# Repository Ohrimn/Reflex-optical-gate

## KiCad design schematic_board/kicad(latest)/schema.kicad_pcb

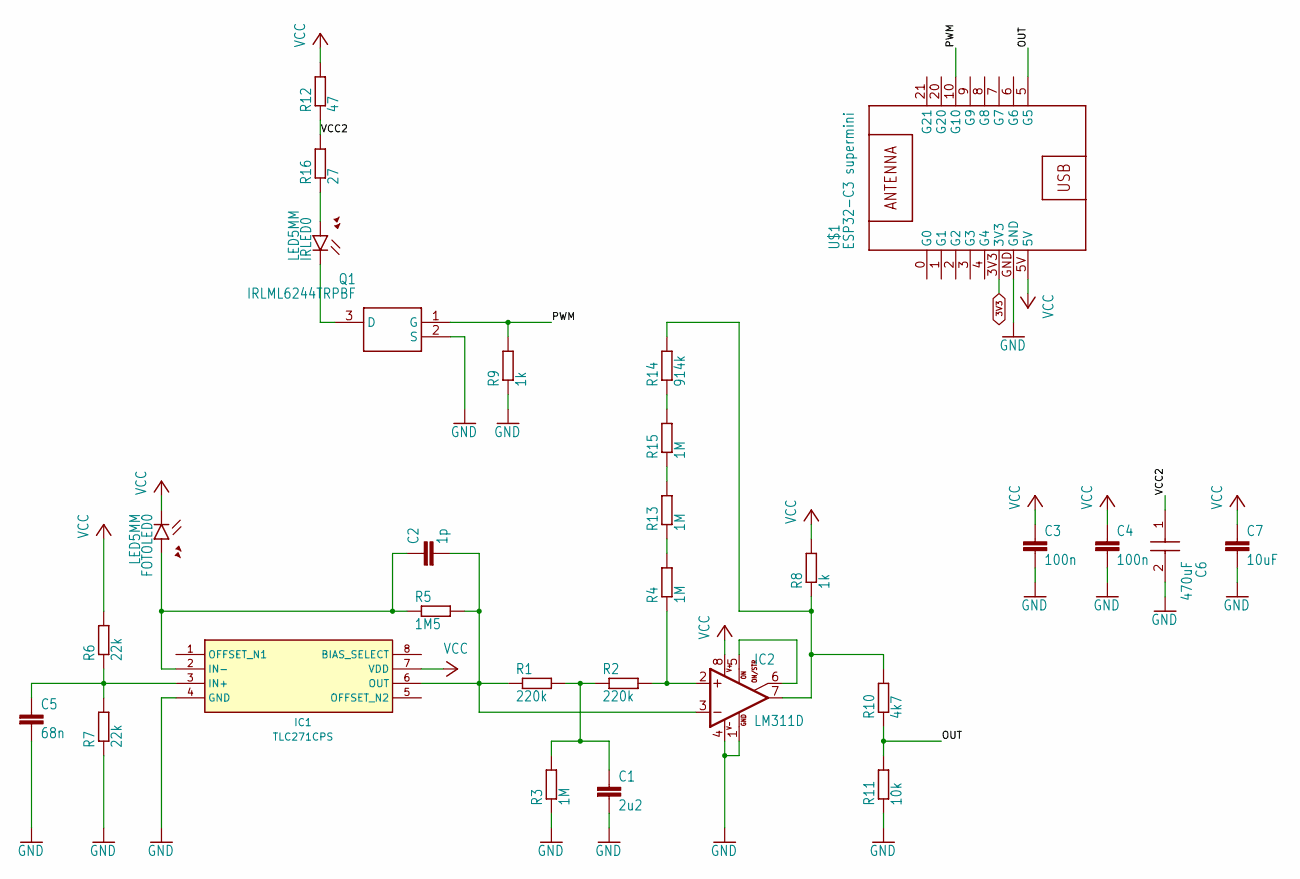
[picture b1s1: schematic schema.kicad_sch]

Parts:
C1: 2u2; C0603
C2: 1p; C0603K
C3, C4: 100n; C0603
C5: 68n; C0603
C6: 470uF; CAPAE830X1100N
C7: 10uF; C0603
FOTOLED0: LED5MM
IC1: TLC271CPS; SOIC-8_3.9x4.9mm_P1.27mm; Mouser Part Number 595-TLC271CPS
IC2: LM311D; SO08
IRLED0: LED5MM
Q1: IRLML6244TRPBF; SOT95P237X112-3N
R1, R2: 220k; R0603
R3, R4, R13, R15: 1M; R0603
R5: 1M5; R0603
R6, R7: 22k; R0603
R8, R9: 1k; R0603
R10: 4k7; R0603
R11: 10k; R0603
R12: 47; R0805
R14: 914k; R0603
R16: 27; R0805
U$1: ESP32-C3 supermini; ESP32-C3_SUPERMINI

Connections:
3V3: U$1.3V3
/OUT: R10.1, R11.2, U$1.5 (G5)
/PWM: Q1.1 (G), R9.2, U$1.10 (G10)
/VCC2: C6.1 (+), R12.1, R16.2
GND: C1.2, C3.2, C4.2, C5.2, C6.2 (-), C7.2, IC1.4 (GND), IC2.1 (GND), IC2.4 (V-), Q1.2 (S), R3.1, R7.1, R9.1, R11.1, U$1.GND
unnamed: C1.1, R1.2, R2.1, R3.2
unnamed: C5.1, IC1.3 (IN+), R6.1, R7.2
unnamed: C2.1, FOTOLED0.A, IC1.2 (IN-), R5.1
unnamed: C2.2, IC1.6 (OUT), IC2.3 (-IN), R1.1, R5.2
unnamed: IC2.2 (+IN), R2.2, R4.1
unnamed: IC2.5 (ON), IC2.6 (ON/STR)
unnamed: IC2.7 (OUT), R8.1, R10.2, R14.2
unnamed: IRLED0.K (C), Q1.3 (D)
unnamed: IRLED0.A, R16.1
unnamed: R4.2, R13.1
unnamed: R13.2, R15.1
unnamed: R14.1, R15.2
VCC: C3.1, C4.1, C7.1, FOTOLED0.K (C), IC1.7 (VDD), IC2.8 (V+), R6.2, R8.2, R12.2, U$1.5V

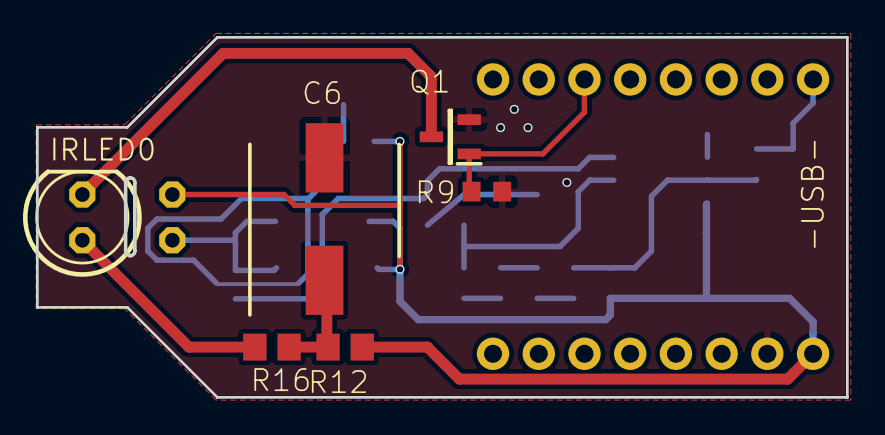
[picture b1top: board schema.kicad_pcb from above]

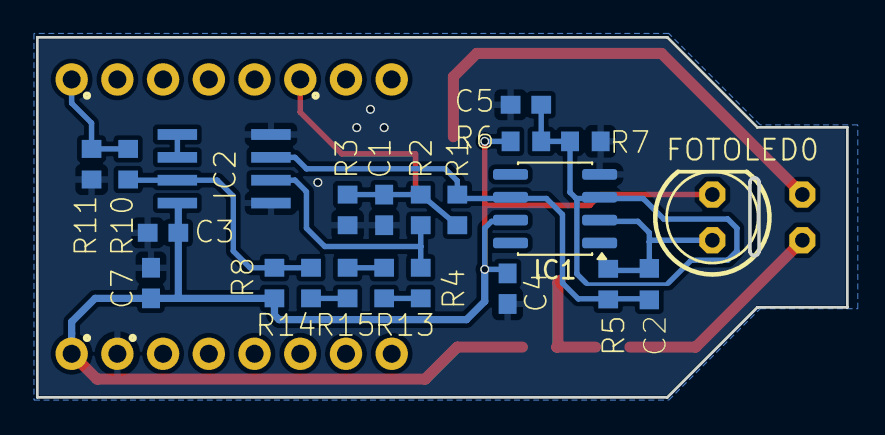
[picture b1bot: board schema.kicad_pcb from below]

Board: 2 copper layers, 44.9 x 19.9 mm, 29 parts (22 on the bottom side), 17 nets.

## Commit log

2026-03-03 Initial release
2026-03-03 test
2026-03-03 Rename ahoj jsem tu.txt to ahoj.txt
2026-03-03 Latest code changes
2026-03-04 Latest schematic and board design
2026-03-04 Latest śchematic and board design
